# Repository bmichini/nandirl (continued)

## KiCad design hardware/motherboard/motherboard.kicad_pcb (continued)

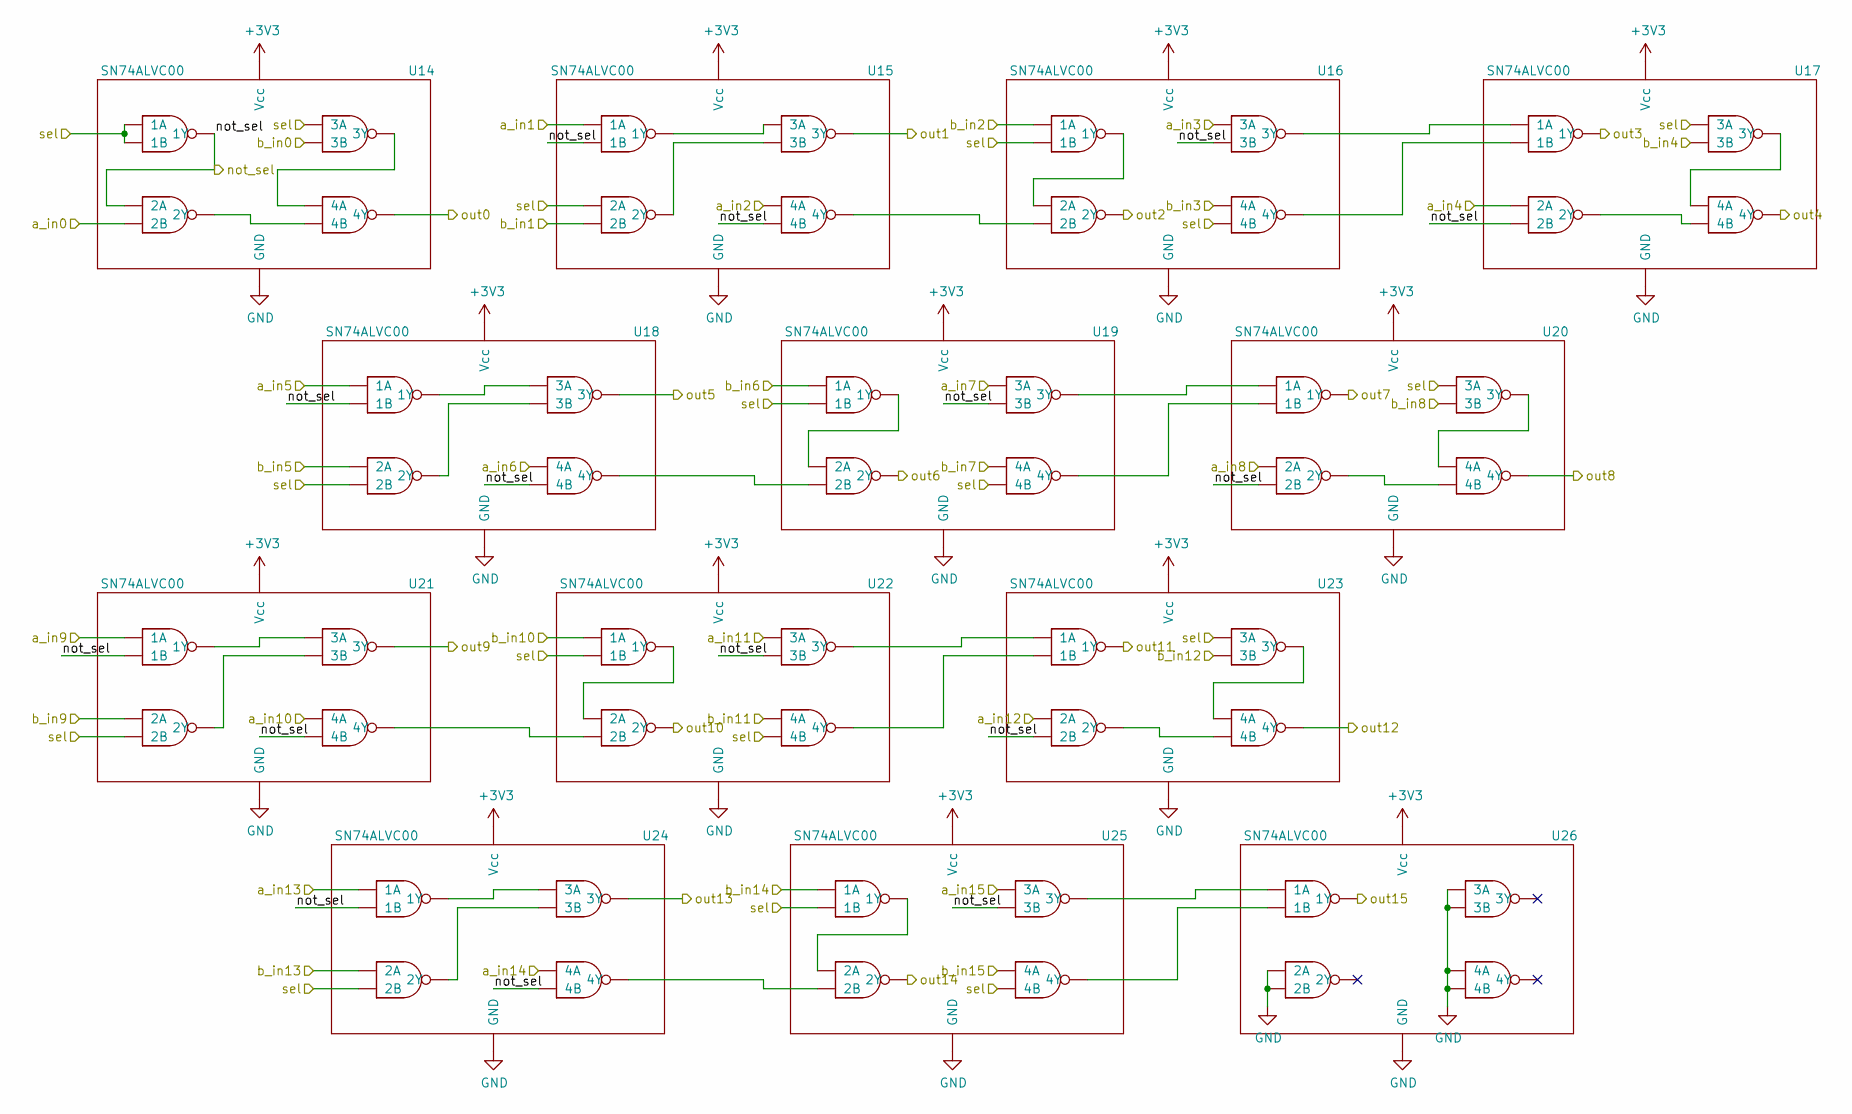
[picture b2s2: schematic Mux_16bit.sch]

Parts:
U1, U2, U3, U4, U5, U6, U7, U8, U9, U10, U11, U12, U13: SN74ALVC00; TSSOP-14_4.4x5mm_P0.65mm; Digikey PN 296-5104-1-ND

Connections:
+3V3: U1.14 (Vcc), U2.14 (Vcc), U3.14 (Vcc), U4.14 (Vcc), U5.14 (Vcc), U6.14 (Vcc), U7.14 (Vcc), U8.14 (Vcc), U9.14 (Vcc), U10.14 (Vcc), U11.14 (Vcc), U12.14 (Vcc), U13.14 (Vcc); also elsewhere on the board
/Mux_16bit/not_sel: U1.3 (1Y), U1.4 (2A), U2.2 (1B), U2.13 (4B), U3.10 (3B), U4.5 (2B), U5.2 (1B), U5.13 (4B), U6.10 (3B), U7.5 (2B), U8.2 (1B), U8.13 (4B), U9.10 (3B), U10.5 (2B), U11.2 (1B), U11.13 (4B), U12.10 (3B)
GND: U1.7 (GND), U2.7 (GND), U3.7 (GND), U4.7 (GND), U5.7 (GND), U6.7 (GND), U7.7 (GND), U8.7 (GND), U9.7 (GND), U10.7 (GND), U11.7 (GND), U12.7 (GND), U13.4 (2A), U13.5 (2B), U13.7 (GND), U13.9 (3A), U13.10 (3B), U13.12 (4A), U13.13 (4B); also elsewhere on the board
unnamed: U1.8 (3Y), U1.12 (4A)
unnamed: U1.6 (2Y), U1.13 (4B)
unnamed: U2.3 (1Y), U2.9 (3A)
unnamed: U2.6 (2Y), U2.10 (3B)
unnamed: U2.11 (4Y), U3.5 (2B)
unnamed: U3.3 (1Y), U3.4 (2A)
unnamed: U3.8 (3Y), U4.1 (1A)
unnamed: U3.11 (4Y), U4.2 (1B)
unnamed: U4.8 (3Y), U4.12 (4A)
unnamed: U4.6 (2Y), U4.13 (4B)
unnamed: U5.3 (1Y), U5.9 (3A)
unnamed: U5.6 (2Y), U5.10 (3B)
unnamed: U5.11 (4Y), U6.5 (2B)
unnamed: U6.3 (1Y), U6.4 (2A)
unnamed: U6.8 (3Y), U7.1 (1A)
unnamed: U6.11 (4Y), U7.2 (1B)
unnamed: U7.8 (3Y), U7.12 (4A)
unnamed: U7.6 (2Y), U7.13 (4B)
unnamed: U8.3 (1Y), U8.9 (3A)
unnamed: U8.6 (2Y), U8.10 (3B)
unnamed: U8.11 (4Y), U9.5 (2B)
unnamed: U9.3 (1Y), U9.4 (2A)
unnamed: U9.8 (3Y), U10.1 (1A)
unnamed: U9.11 (4Y), U10.2 (1B)
unnamed: U10.8 (3Y), U10.12 (4A)
unnamed: U10.6 (2Y), U10.13 (4B)
unnamed: U11.3 (1Y), U11.9 (3A)
unnamed: U11.6 (2Y), U11.10 (3B)
unnamed: U11.11 (4Y), U12.5 (2B)
unnamed: U12.3 (1Y), U12.4 (2A)
unnamed: U12.8 (3Y), U13.1 (1A)
unnamed: U12.11 (4Y), U13.2 (1B)
areg_out0: U1.5 (2B); also elsewhere on the board
areg_out1: U2.1 (1A); also elsewhere on the board
areg_out2: U2.12 (4A); also elsewhere on the board
areg_out3: U3.9 (3A); also elsewhere on the board
areg_out4: U4.4 (2A); also elsewhere on the board
areg_out5: U5.1 (1A); also elsewhere on the board
areg_out6: U5.12 (4A); also elsewhere on the board
areg_out7: U6.9 (3A); also elsewhere on the board
areg_out8: U7.4 (2A); also elsewhere on the board
areg_out9: U8.1 (1A); also elsewhere on the board
areg_out10: U8.12 (4A); also elsewhere on the board
areg_out11: U9.9 (3A); also elsewhere on the board
areg_out12: U10.4 (2A); also elsewhere on the board
areg_out13: U11.1 (1A); also elsewhere on the board
areg_out14: U11.12 (4A); also elsewhere on the board
areg_out15: U12.9 (3A); also elsewhere on the board
inst_12: U1.1 (1A), U1.2 (1B), U1.9 (3A), U2.4 (2A), U3.2 (1B), U3.13 (4B), U4.9 (3A), U5.5 (2B), U6.2 (1B), U6.13 (4B), U7.9 (3A), U8.5 (2B), U9.2 (1B), U9.13 (4B), U10.9 (3A), U11.5 (2B), U12.2 (1B), U12.13 (4B); also elsewhere on the board
mem_out0: U1.10 (3B); also elsewhere on the board
mem_out1: U2.5 (2B); also elsewhere on the board
mem_out2: U3.1 (1A); also elsewhere on the board
mem_out3: U3.12 (4A); also elsewhere on the board
mem_out4: U4.10 (3B); also elsewhere on the board
mem_out5: U5.4 (2A); also elsewhere on the board
mem_out6: U6.1 (1A); also elsewhere on the board
mem_out7: U6.12 (4A); also elsewhere on the board
mem_out8: U7.10 (3B); also elsewhere on the board
mem_out9: U8.4 (2A); also elsewhere on the board
mem_out10: U9.1 (1A); also elsewhere on the board
mem_out11: U9.12 (4A); also elsewhere on the board
mem_out12: U10.10 (3B); also elsewhere on the board
mem_out13: U11.4 (2A); also elsewhere on the board
mem_out14: U12.1 (1A); also elsewhere on the board
mem_out15: U12.12 (4A); also elsewhere on the board
mux_areg_mem_out0: U1.11 (4Y); also elsewhere on the board
mux_areg_mem_out1: U2.8 (3Y); also elsewhere on the board
mux_areg_mem_out2: U3.6 (2Y); also elsewhere on the board
mux_areg_mem_out3: U4.3 (1Y); also elsewhere on the board
mux_areg_mem_out4: U4.11 (4Y); also elsewhere on the board
mux_areg_mem_out5: U5.8 (3Y); also elsewhere on the board
mux_areg_mem_out6: U6.6 (2Y); also elsewhere on the board
mux_areg_mem_out7: U7.3 (1Y); also elsewhere on the board
mux_areg_mem_out8: U7.11 (4Y); also elsewhere on the board
mux_areg_mem_out9: U8.8 (3Y); also elsewhere on the board
mux_areg_mem_out10: U9.6 (2Y); also elsewhere on the board
mux_areg_mem_out11: U10.3 (1Y); also elsewhere on the board
mux_areg_mem_out12: U10.11 (4Y); also elsewhere on the board
mux_areg_mem_out13: U11.8 (3Y); also elsewhere on the board
mux_areg_mem_out14: U12.6 (2Y); also elsewhere on the board
mux_areg_mem_out15: U13.3 (1Y); also elsewhere on the board

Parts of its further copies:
U14, U15, U16, U17, U18, U19, U20, U21, U22, U23, U24, U25, U26: SN74ALVC00; TSSOP-14_4.4x5mm_P0.65mm; Digikey PN 296-5104-1-ND

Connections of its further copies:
+3V3: U14.14 (Vcc), U15.14 (Vcc), U16.14 (Vcc), U17.14 (Vcc), U18.14 (Vcc), U19.14 (Vcc), U20.14 (Vcc), U21.14 (Vcc), U22.14 (Vcc), U23.14 (Vcc), U24.14 (Vcc), U25.14 (Vcc), U26.14 (Vcc); also elsewhere on the board
GND: U14.7 (GND), U15.7 (GND), U16.7 (GND), U17.7 (GND), U18.7 (GND), U19.7 (GND), U20.7 (GND), U21.7 (GND), U22.7 (GND), U23.7 (GND), U24.7 (GND), U25.7 (GND), U25.9 (3A), U26.4 (2A), U26.5 (2B), U26.7 (GND), U26.9 (3A), U26.10 (3B), U26.12 (4A), U26.13 (4B); also elsewhere on the board
unnamed: U14.8 (3Y), U14.12 (4A)
unnamed: U14.6 (2Y), U14.13 (4B)
unnamed: U15.3 (1Y), U15.9 (3A)
unnamed: U15.6 (2Y), U15.10 (3B)
unnamed: U15.11 (4Y), U16.5 (2B)
unnamed: U16.3 (1Y), U16.4 (2A)
unnamed: U16.8 (3Y), U17.1 (1A)
unnamed: U16.11 (4Y), U17.2 (1B)
unnamed: U17.8 (3Y), U17.12 (4A)
unnamed: U17.6 (2Y), U17.13 (4B)
unnamed: U18.3 (1Y), U18.9 (3A)
unnamed: U18.6 (2Y), U18.10 (3B)
unnamed: U18.11 (4Y), U19.5 (2B)
unnamed: U19.3 (1Y), U19.4 (2A)
unnamed: U19.8 (3Y), U20.1 (1A)
unnamed: U19.11 (4Y), U20.2 (1B)
unnamed: U20.8 (3Y), U20.12 (4A)
unnamed: U20.6 (2Y), U20.13 (4B)
unnamed: U21.3 (1Y), U21.9 (3A)
unnamed: U21.6 (2Y), U21.10 (3B)
unnamed: U21.11 (4Y), U22.5 (2B)
unnamed: U22.3 (1Y), U22.4 (2A)
unnamed: U22.8 (3Y), U23.1 (1A)
unnamed: U22.11 (4Y), U23.2 (1B)
unnamed: U23.8 (3Y), U23.12 (4A)
unnamed: U23.6 (2Y), U23.13 (4B)
unnamed: U24.3 (1Y), U24.9 (3A)
unnamed: U24.6 (2Y), U24.10 (3B)
unnamed: U24.11 (4Y), U25.5 (2B)
unnamed: U25.3 (1Y), U25.4 (2A)
unnamed: U25.8 (3Y), U26.1 (1A)
unnamed: U25.11 (4Y), U26.2 (1B)
alu_out0: U14.10 (3B); also elsewhere on the board
alu_out1: U15.5 (2B); also elsewhere on the board
alu_out2: U16.1 (1A); also elsewhere on the board
alu_out3: U16.12 (4A); also elsewhere on the board
alu_out4: U17.10 (3B); also elsewhere on the board
alu_out5: U18.4 (2A); also elsewhere on the board
alu_out6: U19.1 (1A); also elsewhere on the board
alu_out7: U19.12 (4A); also elsewhere on the board
alu_out8: U20.10 (3B); also elsewhere on the board
alu_out9: U21.4 (2A); also elsewhere on the board
alu_out10: U22.1 (1A); also elsewhere on the board
alu_out11: U22.12 (4A); also elsewhere on the board
alu_out12: U23.10 (3B); also elsewhere on the board
alu_out13: U24.4 (2A); also elsewhere on the board
alu_out14: U25.1 (1A); also elsewhere on the board
alu_out15: U25.12 (4A); also elsewhere on the board
areg_in0: U14.11 (4Y); also elsewhere on the board
areg_in1: U15.8 (3Y); also elsewhere on the board
areg_in2: U16.6 (2Y); also elsewhere on the board
areg_in3: U17.3 (1Y); also elsewhere on the board
areg_in4: U17.11 (4Y); also elsewhere on the board
areg_in5: U18.8 (3Y); also elsewhere on the board
areg_in6: U19.6 (2Y); also elsewhere on the board
areg_in7: U20.3 (1Y); also elsewhere on the board
areg_in8: U20.11 (4Y); also elsewhere on the board
areg_in9: U21.8 (3Y); also elsewhere on the board
areg_in10: U22.6 (2Y); also elsewhere on the board
areg_in11: U23.3 (1Y); also elsewhere on the board
areg_in12: U23.11 (4Y); also elsewhere on the board
areg_in13: U24.8 (3Y); also elsewhere on the board
areg_in14: U25.6 (2Y); also elsewhere on the board
areg_in15: U26.3 (1Y); also elsewhere on the board
inst_0: U14.5 (2B); also elsewhere on the board
inst_1: U15.1 (1A); also elsewhere on the board
inst_2: U15.12 (4A); also elsewhere on the board
inst_3: U16.9 (3A); also elsewhere on the board
inst_4: U17.4 (2A); also elsewhere on the board
inst_5: U18.1 (1A); also elsewhere on the board
inst_6: U18.12 (4A); also elsewhere on the board
inst_7: U19.9 (3A); also elsewhere on the board
inst_8: U20.4 (2A); also elsewhere on the board
inst_9: U21.1 (1A); also elsewhere on the board
inst_10: U21.12 (4A); also elsewhere on the board
inst_11: U22.9 (3A); also elsewhere on the board
inst_12: U23.4 (2A); also elsewhere on the board
inst_13: U24.1 (1A); also elsewhere on the board
inst_14: U24.12 (4A); also elsewhere on the board
inst_15: U14.1 (1A), U14.2 (1B), U14.9 (3A), U15.4 (2A), U16.2 (1B), U16.13 (4B), U17.9 (3A), U18.5 (2B), U19.2 (1B), U19.13 (4B), U20.9 (3A), U21.5 (2B), U22.2 (1B), U22.13 (4B), U23.9 (3A), U24.5 (2B), U25.2 (1B), U25.13 (4B); also elsewhere on the board
~inst_15: U14.3 (1Y), U14.4 (2A), U15.2 (1B), U15.13 (4B), U16.10 (3B), U17.5 (2B), U18.2 (1B), U18.13 (4B), U19.10 (3B), U20.5 (2B), U21.2 (1B), U21.13 (4B), U22.10 (3B), U23.5 (2B), U24.2 (1B), U24.13 (4B), U25.10 (3B); also elsewhere on the board

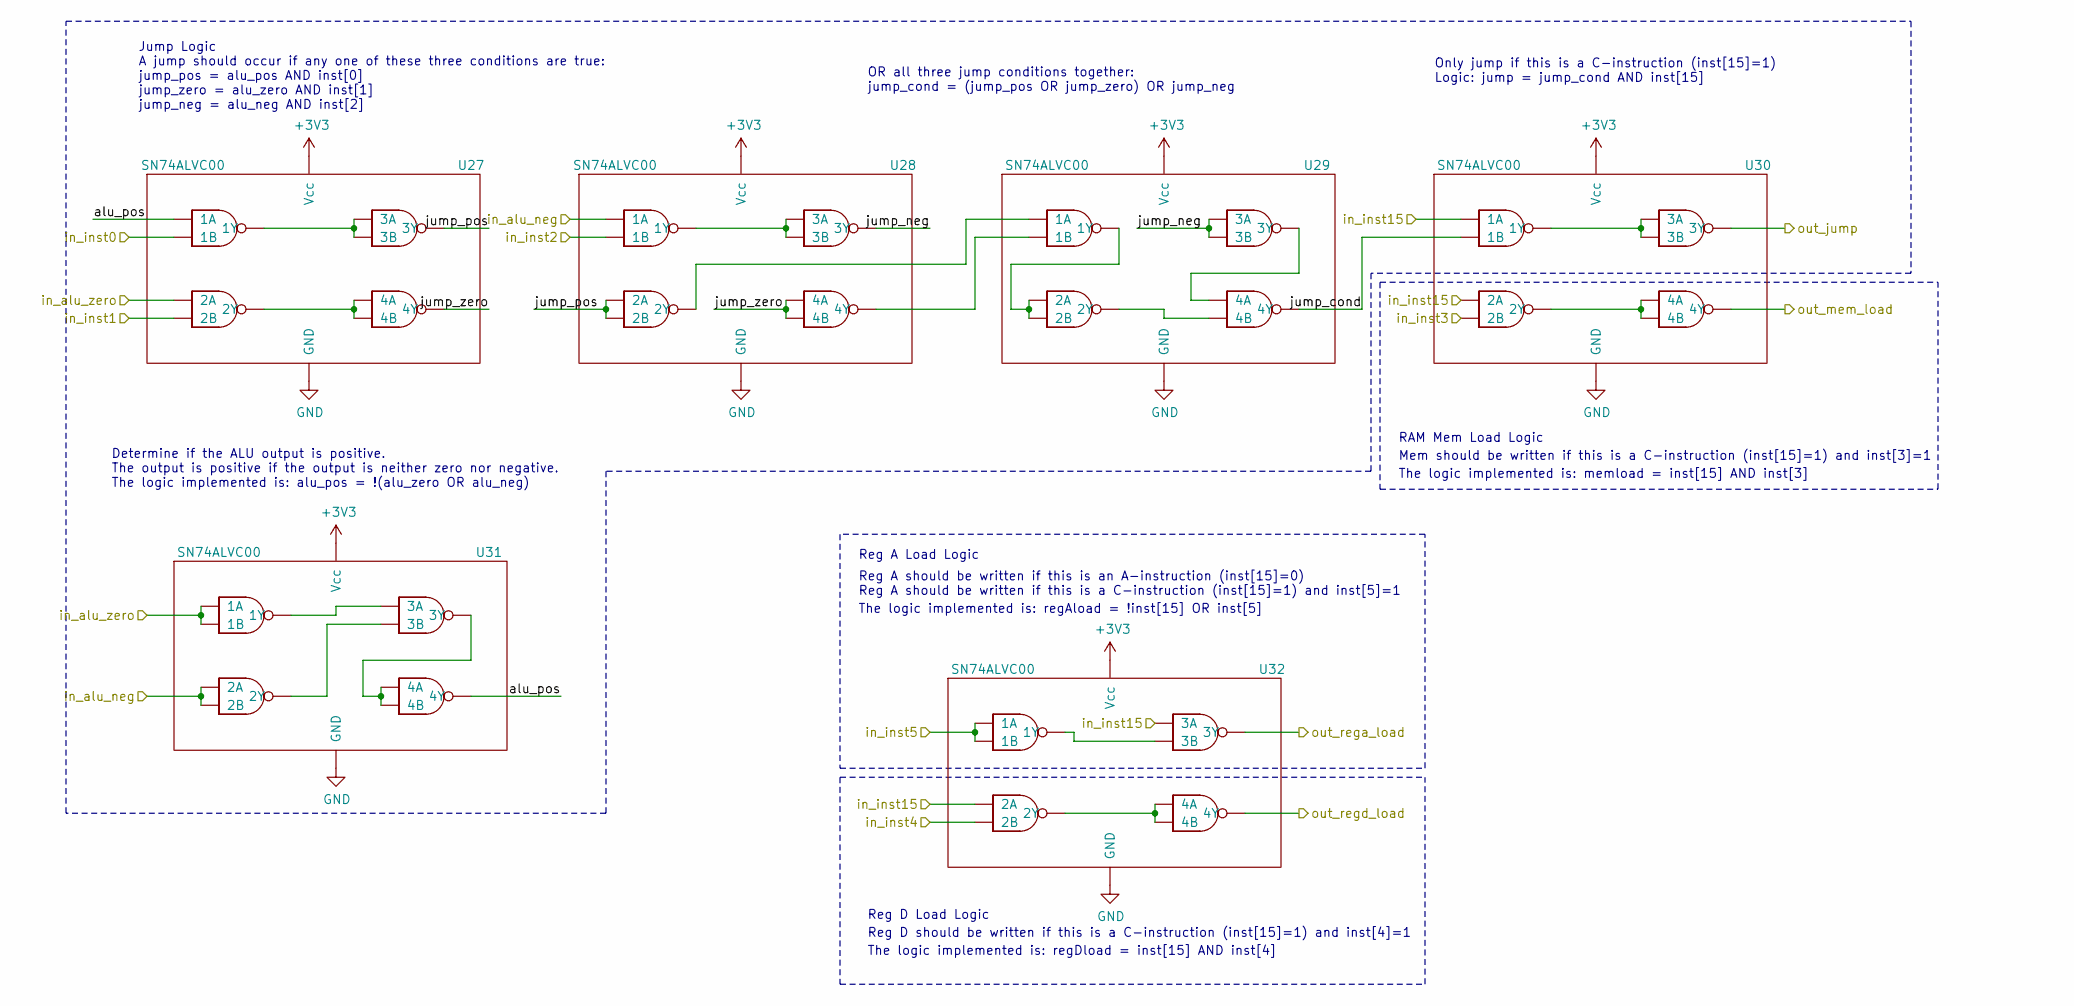
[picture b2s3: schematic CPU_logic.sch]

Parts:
U27, U28, U29, U30, U31, U32: SN74ALVC00; TSSOP-14_4.4x5mm_P0.65mm; Digikey PN 296-5104-1-ND

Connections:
+3V3: U27.14 (Vcc), U28.14 (Vcc), U29.14 (Vcc), U30.14 (Vcc), U31.14 (Vcc), U32.14 (Vcc); also elsewhere on the board
/CPU_logic/alu_pos: U27.1 (1A), U31.11 (4Y)
/CPU_logic/jump_cond: U29.11 (4Y), U30.2 (1B)
/CPU_logic/jump_neg: U28.8 (3Y), U29.9 (3A), U29.10 (3B)
/CPU_logic/jump_pos: U27.8 (3Y), U28.4 (2A), U28.5 (2B)
/CPU_logic/jump_zero: U27.11 (4Y), U28.12 (4A), U28.13 (4B)
GND: U27.7 (GND), U28.7 (GND), U29.7 (GND), U30.7 (GND), U31.7 (GND), U32.7 (GND); also elsewhere on the board
unnamed: U27.3 (1Y), U27.9 (3A), U27.10 (3B)
unnamed: U27.6 (2Y), U27.12 (4A), U27.13 (4B)
unnamed: U28.6 (2Y), U29.1 (1A)
unnamed: U28.3 (1Y), U28.9 (3A), U28.10 (3B)
unnamed: U28.11 (4Y), U29.2 (1B)
unnamed: U29.3 (1Y), U29.4 (2A), U29.5 (2B)
unnamed: U29.8 (3Y), U29.12 (4A)
unnamed: U29.6 (2Y), U29.13 (4B)
unnamed: U30.3 (1Y), U30.9 (3A), U30.10 (3B)
unnamed: U30.6 (2Y), U30.12 (4A), U30.13 (4B)
unnamed: U31.3 (1Y), U31.9 (3A)
unnamed: U31.6 (2Y), U31.10 (3B)
unnamed: U31.8 (3Y), U31.12 (4A), U31.13 (4B)
unnamed: U32.3 (1Y), U32.10 (3B)
unnamed: U32.6 (2Y), U32.12 (4A), U32.13 (4B)
alu_neg: U28.1 (1A), U31.4 (2A), U31.5 (2B); also elsewhere on the board
alu_zero: U27.4 (2A), U31.1 (1A), U31.2 (1B); also elsewhere on the board
inst_0: U27.2 (1B); also elsewhere on the board
inst_1: U27.5 (2B); also elsewhere on the board
inst_2: U28.2 (1B); also elsewhere on the board
inst_3: U30.5 (2B); also elsewhere on the board
inst_4: U32.5 (2B); also elsewhere on the board
inst_5: U32.1 (1A), U32.2 (1B); also elsewhere on the board
inst_15: U30.1 (1A), U30.4 (2A), U32.4 (2A), U32.9 (3A); also elsewhere on the board
mem_load: U30.11 (4Y); also elsewhere on the board
pc_load: U30.8 (3Y); also elsewhere on the board
rega_load: U32.8 (3Y); also elsewhere on the board
regd_load: U32.11 (4Y); also elsewhere on the board

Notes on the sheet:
Reg A Load Logic
Reg A should be written if this is an A-instruction (inst[15]=0) Reg A should be written if this is a C-instruction (inst[15]=1) and inst[5]=1
The logic implemented is: regAload = !inst[15] OR inst[5]
Reg D Load Logic
The logic implemented is: regDload = inst[15] AND inst[4]
Reg D should be written if this is a C-instruction (inst[15]=1) and inst[4]=1
Determine if the ALU output is positive. The output is positive if the output is neither zero nor negative. The logic implemented is: alu_pos = !(alu_zero OR alu_neg)
Jump Logic A jump should occur if any one of these three conditions are true: jump_pos = alu_pos AND inst[0] jump_zero = alu_zero AND inst[1] jump_neg = alu_neg AND inst[2]
OR all three jump conditions together: jump_cond = (jump_pos OR jump_zero) OR jump_neg
Only jump if this is a C-instruction (inst[15]=1) Logic: jump = jump_cond AND inst[15]
RAM Mem Load Logic
The logic implemented is: memload = inst[15] AND inst[3]
Mem should be written if this is a C-instruction (inst[15]=1) and inst[3]=1

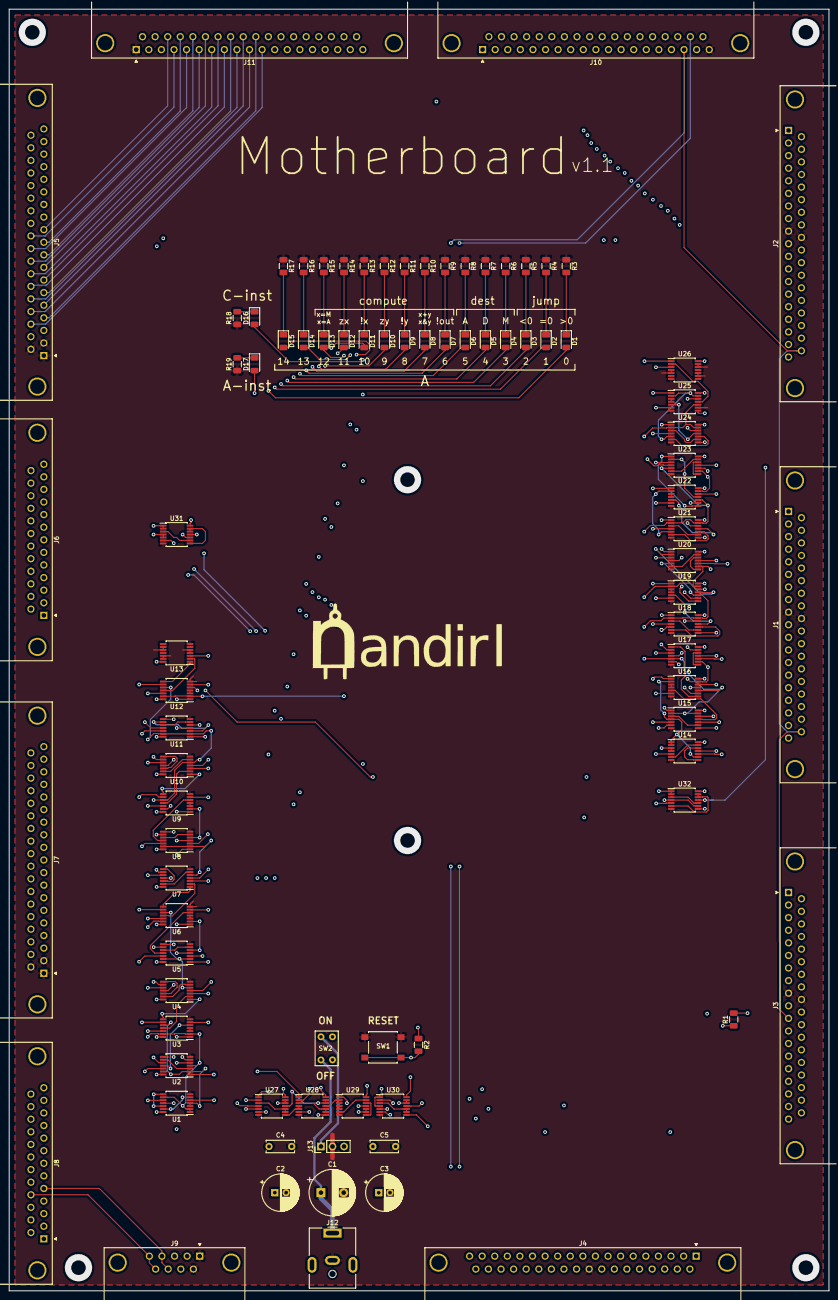
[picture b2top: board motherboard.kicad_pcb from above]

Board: 4 copper layers, 180.3 x 281.9 mm, 88 parts (0 on the bottom side), 247 nets.

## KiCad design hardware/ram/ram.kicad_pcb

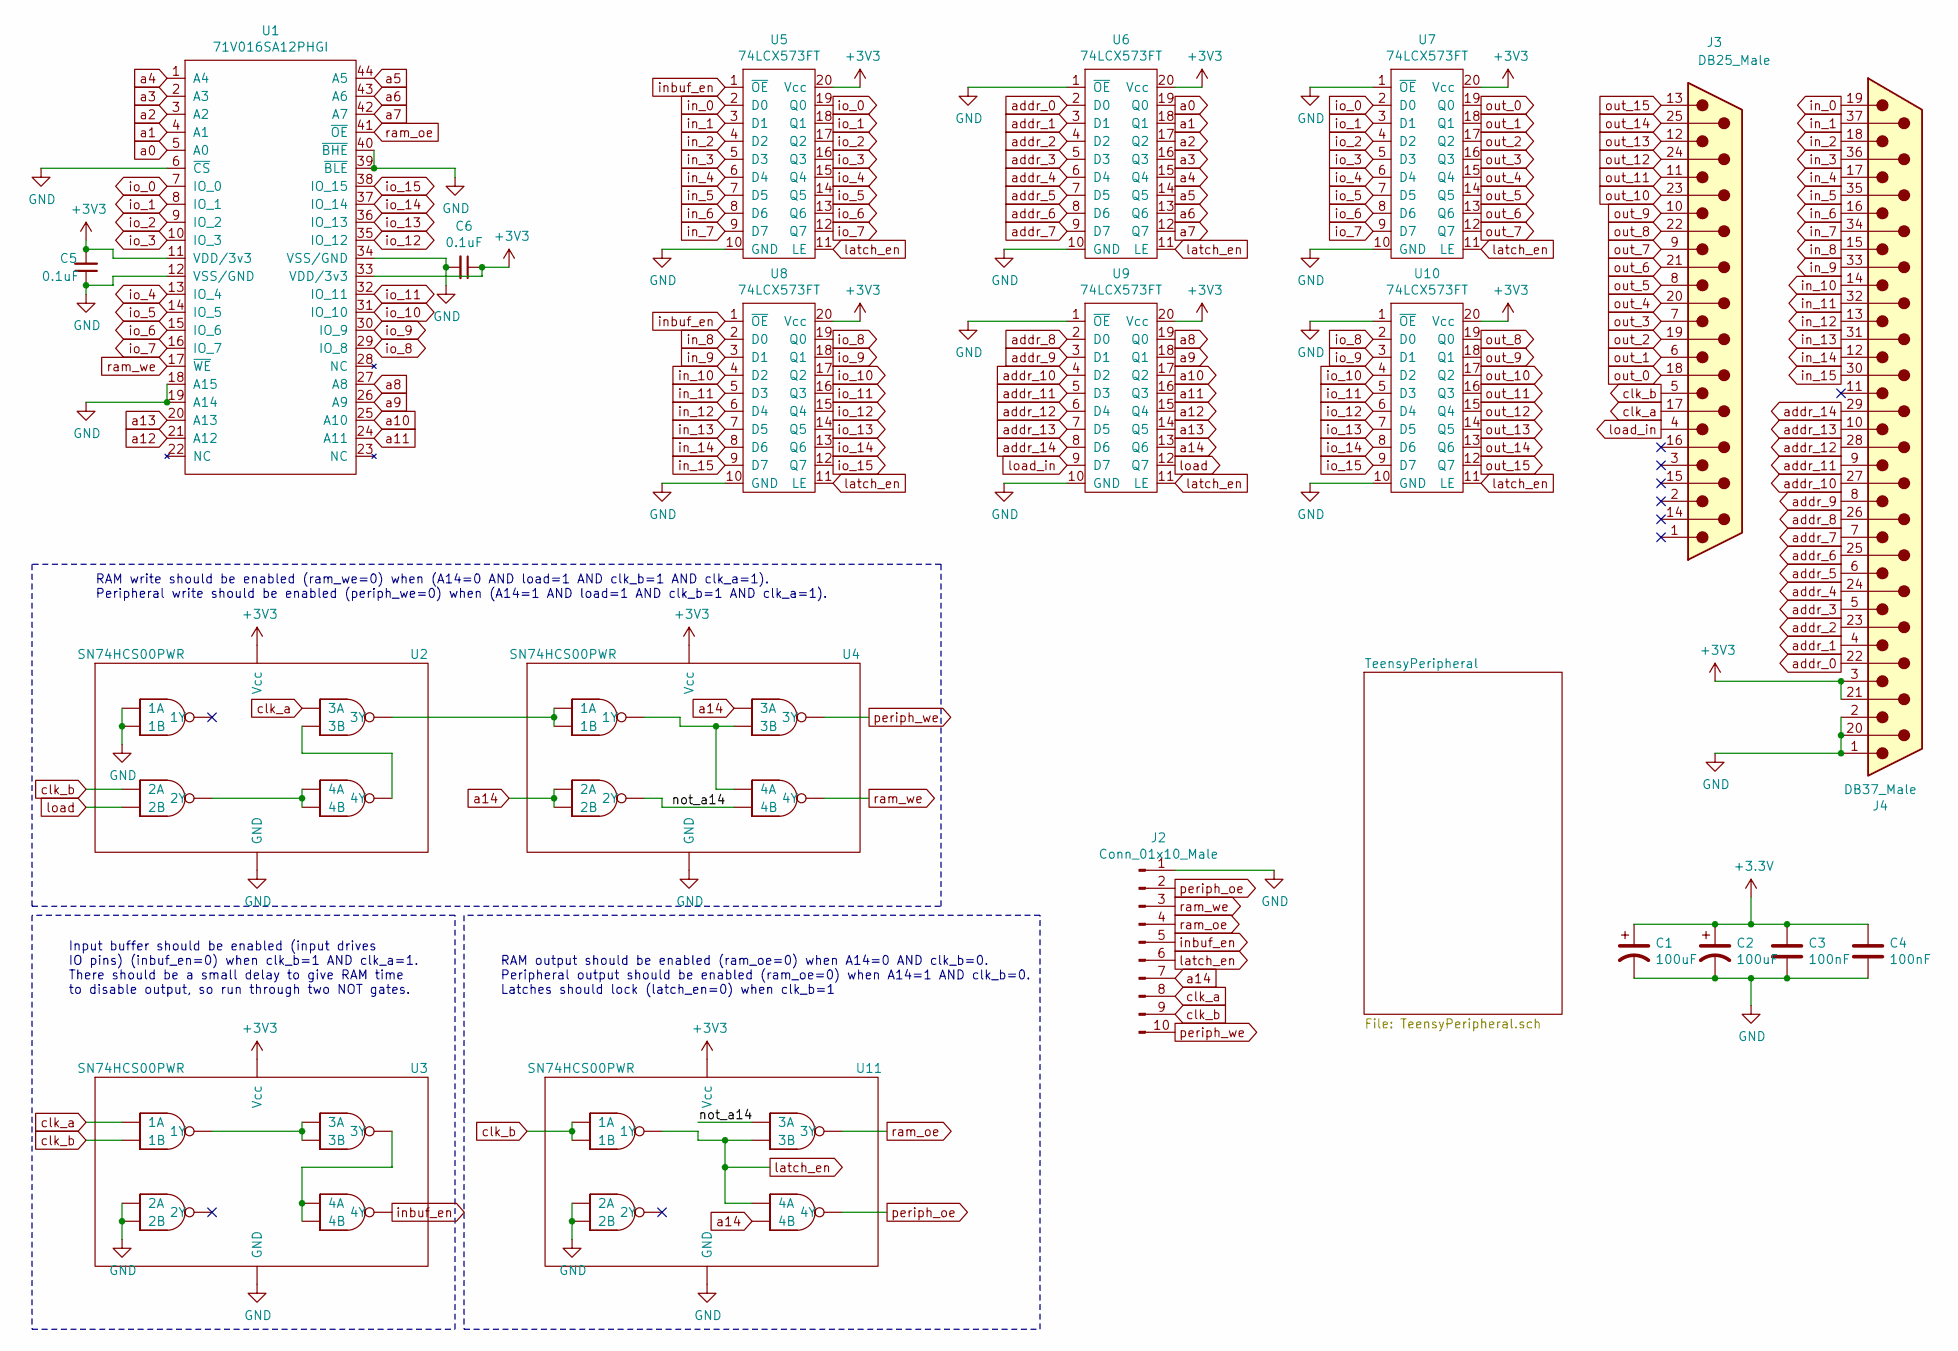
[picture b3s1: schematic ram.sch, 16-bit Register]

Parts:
C1, C2: 100uF; CP_Radial_D8.0mm_P2.50mm; Digikey PN P15797CT-ND
C3, C4: 100nF; C_Disc_D5.0mm_W2.5mm_P5.00mm; Digikey PN BC5229CT-ND
C5, C6: 0.1uF; C_1206_3216Metric; Digikey PN 399-C1206C104K5RAC7800CT-ND
J2: Conn_01x10_Male; PinHeader_1x10_P2.54mm_Vertical
J3: DB25_Male; DSUB-25_Male_Horizontal_P2.77x2.84mm_EdgePinOffset7.70mm_Ho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; Digikey PN AE10980-ND
J4: DB37_Male; DSUB-37_Male_Horizontal_P2.77x2.84mm_EdgePinOffset7.70mm_Ho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; Digikey PN AE10986-ND
U1: 71V016SA12PHGI; TSOP-II-44_10.16x18.41mm_P0.8mm; Digikey PN 800-2609-5-ND
U2, U3, U4, U11: SN74HCS00PWR; TSSOP-14_4.4x5mm_P0.65mm; Digikey PN 296-SN74HCS00PWRCT-ND
U5, U6, U7, U8, U9, U10: 74LCX573FT; TSSOP-20_4.4x6.5mm_P0.65mm; Digikey PN 74LCX573FT(AJ)CT-ND

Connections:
/not_a14: U4.6 (2Y), U4.13 (4B), U11.9 (3A)
GND: C1.2, C2.2, C3.2, C4.2, C5.1, C6.2, J2.1, J4.1, J4.2, J4.20, U1.6 (~CS), U1.12 (VSS/GND), U1.18 (A15), U1.19 (A14), U1.34 (VSS/GND), U1.39 (~BLE), U1.40 (~BHE), U2.1 (1A), U2.2 (1B), U2.7 (GND), U3.4 (2A), U3.5 (2B), U3.7 (GND), U4.7 (GND), U5.10 (GND), U6.1 (~OE), U6.10 (GND), U7.1 (~OE), U7.10 (GND), U8.10 (GND), U9.1 (~OE), U9.10 (GND), U10.1 (~OE), U10.10 (GND), U11.4 (2A), U11.5 (2B), U11.7 (GND); also elsewhere on the board
unnamed: U2.8 (3Y), U4.1 (1A), U4.2 (1B)
unnamed: U2.10 (3B), U2.11 (4Y)
unnamed: U2.6 (2Y), U2.12 (4A), U2.13 (4B)
unnamed: U3.3 (1Y), U3.9 (3A), U3.10 (3B)
unnamed: U3.8 (3Y), U3.12 (4A), U3.13 (4B)
unnamed: U4.3 (1Y), U4.10 (3B), U4.12 (4A)
a0: U1.5 (A0), U6.19 (Q0); also elsewhere on the board
a1: U1.4 (A1), U6.18 (Q1); also elsewhere on the board
a2: U1.3 (A2), U6.17 (Q2); also elsewhere on the board
a3: U1.2 (A3), U6.16 (Q3); also elsewhere on the board
a4: U1.1 (A4), U6.15 (Q4); also elsewhere on the board
a5: U1.44 (A5), U6.14 (Q5); also elsewhere on the board
a6: U1.43 (A6), U6.13 (Q6); also elsewhere on the board
a7: U1.42 (A7), U6.12 (Q7); also elsewhere on the board
a8: U1.27 (A8), U9.19 (Q0); also elsewhere on the board
a9: U1.26 (A9), U9.18 (Q1); also elsewhere on the board
a10: U1.25 (A10), U9.17 (Q2); also elsewhere on the board
a11: U1.24 (A11), U9.16 (Q3); also elsewhere on the board
a12: U1.21 (A12), U9.15 (Q4); also elsewhere on the board
a13: U1.20 (A13), U9.14 (Q5); also elsewhere on the board
a14: J2.7, U4.4 (2A), U4.5 (2B), U4.9 (3A), U9.13 (Q6), U11.13 (4B); also elsewhere on the board
addr_0: J4.22, U6.2 (D0)
addr_1: J4.4, U6.3 (D1)
addr_2: J4.23, U6.4 (D2)
addr_3: J4.5, U6.5 (D3)
addr_4: J4.24, U6.6 (D4)
addr_5: J4.6, U6.7 (D5)
addr_6: J4.25, U6.8 (D6)
addr_7: J4.7, U6.9 (D7)
addr_8: J4.26, U9.2 (D0)
addr_9: J4.8, U9.3 (D1)
addr_10: J4.27, U9.4 (D2)
addr_11: J4.9, U9.5 (D3)
addr_12: J4.28, U9.6 (D4)
addr_13: J4.10, U9.7 (D5)
addr_14: J4.29, U9.8 (D6)
clk_a: J2.8, J3.17, U2.9 (3A), U3.1 (1A); also elsewhere on the board
clk_b: J2.9, J3.5, U2.4 (2A), U3.2 (1B), U11.1 (1A), U11.2 (1B); also elsewhere on the board
in_0: J4.19, U5.2 (D0)
in_1: J4.37, U5.3 (D1)
in_2: J4.18, U5.4 (D2)
in_3: J4.36, U5.5 (D3)
in_4: J4.17, U5.6 (D4)
in_5: J4.35, U5.7 (D5)
in_6: J4.16, U5.8 (D6)
in_7: J4.34, U5.9 (D7)
in_8: J4.15, U8.2 (D0)
in_9: J4.33, U8.3 (D1)
in_10: J4.14, U8.4 (D2)
in_11: J4.32, U8.5 (D3)
in_12: J4.13, U8.6 (D4)
in_13: J4.31, U8.7 (D5)
in_14: J4.12, U8.8 (D6)
in_15: J4.30, U8.9 (D7)
inbuf_en: J2.5, U3.11 (4Y), U5.1 (~OE), U8.1 (~OE)
io_0: U1.7 (IO_0), U5.19 (Q0), U7.2 (D0); also elsewhere on the board
io_1: U1.8 (IO_1), U5.18 (Q1), U7.3 (D1); also elsewhere on the board
io_2: U1.9 (IO_2), U5.17 (Q2), U7.4 (D2); also elsewhere on the board
io_3: U1.10 (IO_3), U5.16 (Q3), U7.5 (D3); also elsewhere on the board
io_4: U1.13 (IO_4), U5.15 (Q4), U7.6 (D4); also elsewhere on the board
io_5: U1.14 (IO_5), U5.14 (Q5), U7.7 (D5); also elsewhere on the board
io_6: U1.15 (IO_6), U5.13 (Q6), U7.8 (D6); also elsewhere on the board
io_7: U1.16 (IO_7), U5.12 (Q7), U7.9 (D7); also elsewhere on the board
io_8: U1.29 (IO_8), U8.19 (Q0), U10.2 (D0); also elsewhere on the board
io_9: U1.30 (IO_9), U8.18 (Q1), U10.3 (D1); also elsewhere on the board
io_10: U1.31 (IO_10), U8.17 (Q2), U10.4 (D2); also elsewhere on the board
io_11: U1.32 (IO_11), U8.16 (Q3), U10.5 (D3); also elsewhere on the board
io_12: U1.35 (IO_12), U8.15 (Q4), U10.6 (D4); also elsewhere on the board
io_13: U1.36 (IO_13), U8.14 (Q5), U10.7 (D5); also elsewhere on the board
io_14: U1.37 (IO_14), U8.13 (Q6), U10.8 (D6); also elsewhere on the board
io_15: U1.38 (IO_15), U8.12 (Q7), U10.9 (D7); also elsewhere on the board
latch_en: J2.6, U5.11 (LE), U6.11 (LE), U7.11 (LE), U8.11 (LE), U9.11 (LE), U10.11 (LE), U11.3 (1Y), U11.10 (3B), U11.12 (4A)
load: U2.5 (2B), U9.12 (Q7); also elsewhere on the board
load_in: J3.4, U9.9 (D7)
out_0: J3.18, U7.19 (Q0)
out_1: J3.6, U7.18 (Q1)
out_2: J3.19, U7.17 (Q2)
out_3: J3.7, U7.16 (Q3)
out_4: J3.20, U7.15 (Q4)
out_5: J3.8, U7.14 (Q5)
out_6: J3.21, U7.13 (Q6)
out_7: J3.9, U7.12 (Q7)
out_8: J3.22, U10.19 (Q0)
out_9: J3.10, U10.18 (Q1)
out_10: J3.23, U10.17 (Q2)
out_11: J3.11, U10.16 (Q3)
out_12: J3.24, U10.15 (Q4)
out_13: J3.12, U10.14 (Q5)
out_14: J3.25, U10.13 (Q6)
out_15: J3.13, U10.12 (Q7)
periph_oe: J2.2, U11.11 (4Y); also elsewhere on the board
periph_we: J2.10, U4.8 (3Y); also elsewhere on the board
ram_oe: J2.4, U1.41 (~OE), U11.8 (3Y)
ram_we: J2.3, U1.17 (~WE), U4.11 (4Y)

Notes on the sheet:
Input buffer should be enabled (input drives IO pins) (inbuf_en=0) when clk_b=1 AND clk_a=1. There should be a small delay to give RAM time to disable output, so run through two NOT gates.
RAM write should be enabled (ram_we=0) when (A14=0 AND load=1 AND clk_b=1 AND clk_a=1). Peripheral write should be enabled (periph_we=0) when (A14=1 AND load=1 AND clk_b=1 AND clk_a=1).
RAM output should be enabled (ram_oe=0) when A14=0 AND clk_b=0. Peripheral output should be enabled (ram_oe=0) when A14=1 AND clk_b=0. Latches should lock (latch_en=0) when clk_b=1

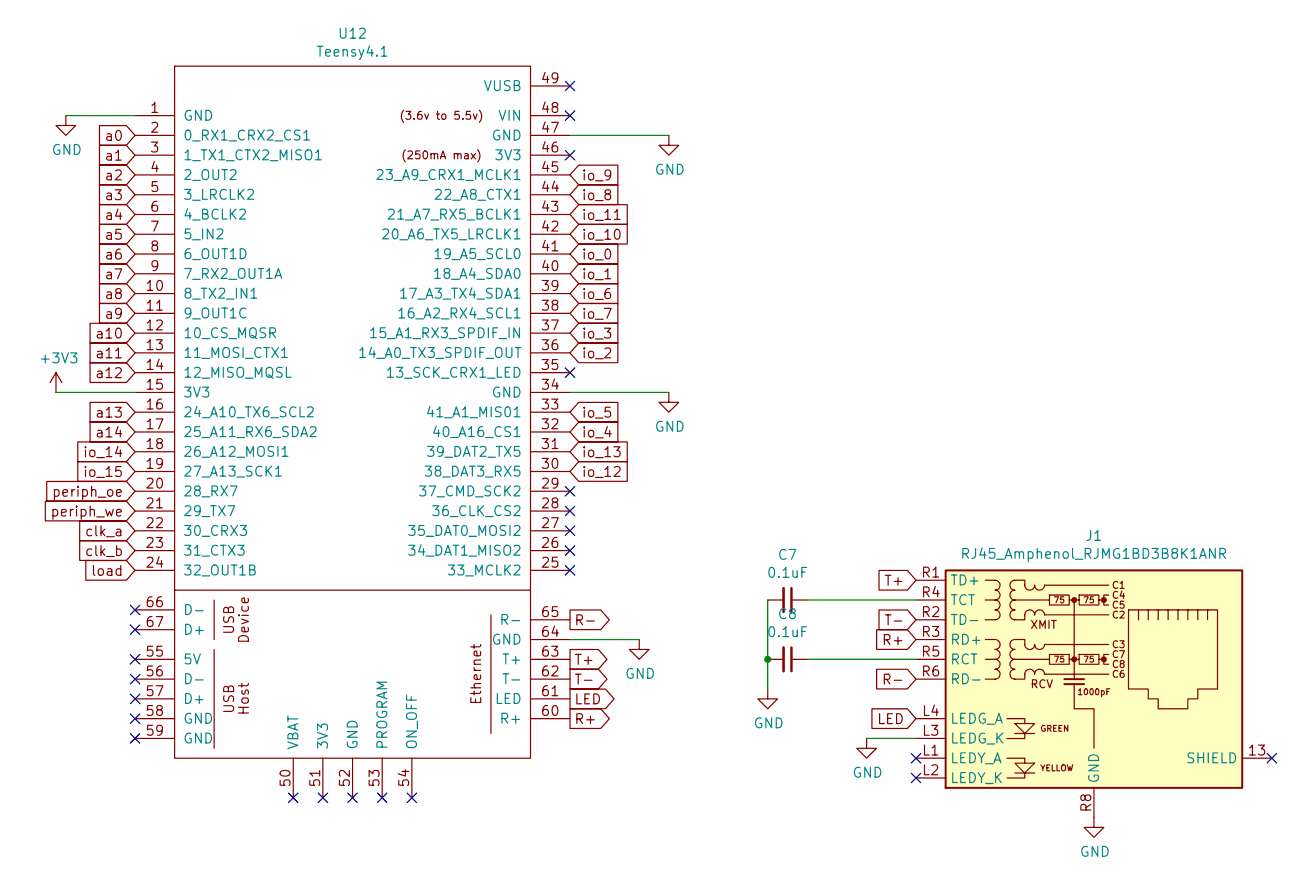
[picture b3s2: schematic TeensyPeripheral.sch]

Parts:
C7, C8: 0.1uF; C_1206_3216Metric; Digikey PN 399-C1206C104K5RAC7800CT-ND
J1: RJ45_Amphenol_RJMG1BD3B8K1ANR; Digikey PN RJMG1BD3B8K1ANR-ND
U12: Teensy4.1; Teensy41

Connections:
GND: C7.2, C8.2, J1.L3 (LEDG_K), J1.R8 (GND), U12.1 (GND), U12.34 (GND), U12.47 (GND), U12.64 (GND); also elsewhere on the board
LED: J1.L4 (LEDG_A), U12.61 (LED)
unnamed: C7.1, J1.R4 (TCT)
unnamed: C8.1, J1.R5 (RCT)
R+: J1.R3 (RD+), U12.60 (R+)
R-: J1.R6 (RD-), U12.65 (R-)
T+: J1.R1 (TD+), U12.63 (T+)
T-: J1.R2 (TD-), U12.62 (T-)
a0: U12.2 (0_RX1_CRX2_CS1); also elsewhere on the board
a1: U12.3 (1_TX1_CTX2_MISO1); also elsewhere on the board
a2: U12.4 (2_OUT2); also elsewhere on the board
a3: U12.5 (3_LRCLK2); also elsewhere on the board
a4: U12.6 (4_BCLK2); also elsewhere on the board
a5: U12.7 (5_IN2); also elsewhere on the board
a6: U12.8 (6_OUT1D); also elsewhere on the board
a7: U12.9 (7_RX2_OUT1A); also elsewhere on the board
a8: U12.10 (8_TX2_IN1); also elsewhere on the board
a9: U12.11 (9_OUT1C); also elsewhere on the board
a10: U12.12 (10_CS_MQSR); also elsewhere on the board
a11: U12.13 (11_MOSI_CTX1); also elsewhere on the board
a12: U12.14 (12_MISO_MQSL); also elsewhere on the board
a13: U12.16 (24_A10_TX6_SCL2); also elsewhere on the board
a14: U12.17 (25_A11_RX6_SDA2); also elsewhere on the board
clk_a: U12.22 (30_CRX3); also elsewhere on the board
clk_b: U12.23 (31_CTX3); also elsewhere on the board
io_0: U12.41 (19_A5_SCL0); also elsewhere on the board
io_1: U12.40 (18_A4_SDA0); also elsewhere on the board
io_2: U12.36 (14_A0_TX3_SPDIF_OUT); also elsewhere on the board
io_3: U12.37 (15_A1_RX3_SPDIF_IN); also elsewhere on the board
io_4: U12.32 (40_A16_CS1); also elsewhere on the board
io_5: U12.33 (41_A1_MIS01); also elsewhere on the board
io_6: U12.39 (17_A3_TX4_SDA1); also elsewhere on the board
io_7: U12.38 (16_A2_RX4_SCL1); also elsewhere on the board
io_8: U12.44 (22_A8_CTX1); also elsewhere on the board
io_9: U12.45 (23_A9_CRX1_MCLK1); also elsewhere on the board
io_10: U12.42 (20_A6_TX5_LRCLK1); also elsewhere on the board
io_11: U12.43 (21_A7_RX5_BCLK1); also elsewhere on the board
io_12: U12.30 (38_DAT3_RX5); also elsewhere on the board
io_13: U12.31 (39_DAT2_TX5); also elsewhere on the board
io_14: U12.18 (26_A12_MOSI1); also elsewhere on the board
io_15: U12.19 (27_A13_SCK1); also elsewhere on the board
load: U12.24 (32_OUT1B); also elsewhere on the board
periph_oe: U12.20 (28_RX7); also elsewhere on the board
periph_we: U12.21 (29_TX7); also elsewhere on the board

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
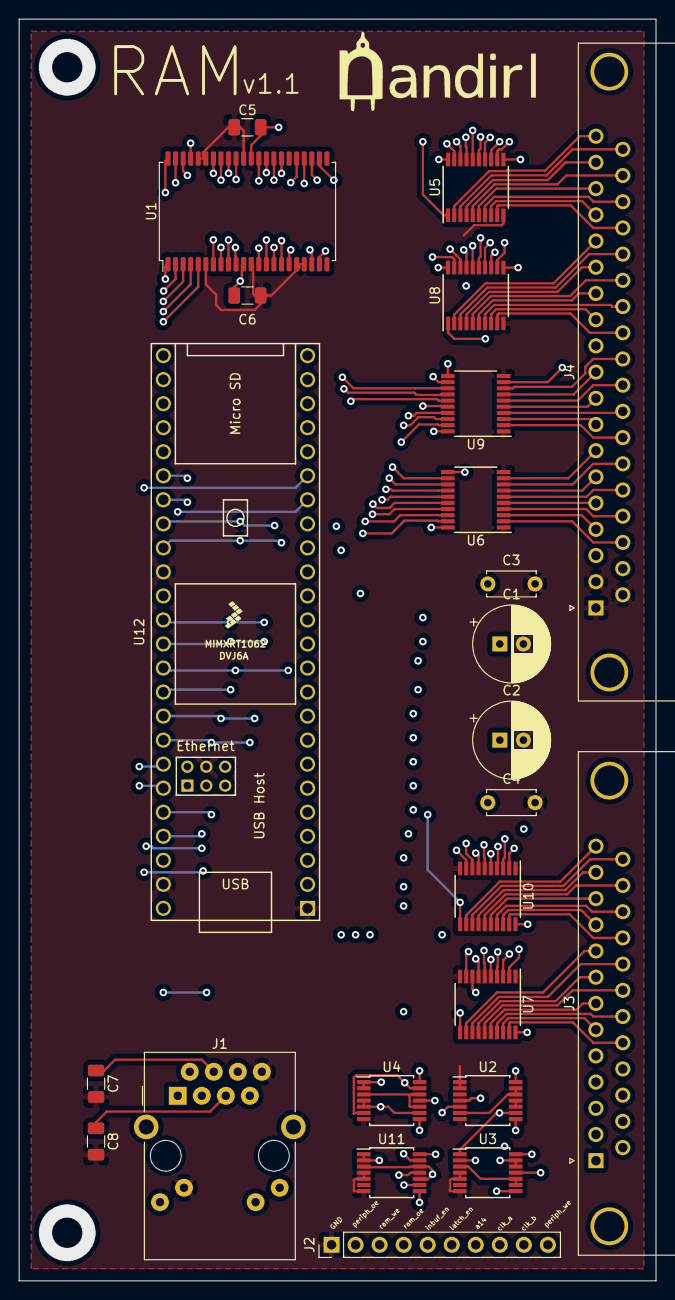
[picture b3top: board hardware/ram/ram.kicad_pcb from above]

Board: 4 copper layers, 67.3 x 133.3 mm, 24 parts (0 on the bottom side), 104 nets.
